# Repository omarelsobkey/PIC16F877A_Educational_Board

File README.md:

# Introduction
we can call it "PIC copy of Arduino". it was designed for educational purposes as I study microcontrollers this semester and the main microcontroller in this course is PIC16F877A.
this board supplies me with the most needed connections for me so allow me to mention them to you

# Features
1. 5x10 cm^2
2. ON/OFF Switch
3. Power input (7:20)v in 4 ways (terminal Block, USB, Power Adapter, Vin pin)
4. Outputs 5v, 3.3v
5. Header for all PIC GPIO pins
6. Programming pins header
7. UART communication using CH340 with jumpers to allow either connecting or disconnecting computer communication

# Versions
this is the 4th version of this board as I always seek additional improvements that will help me make the work easier
- 1st Version was only the main connection of the reset circuit and crystal
- 2nd version supported input power (7:20)v through terminal block
- 3rd version supported the dc jack and added some protection to the power circuit
- 4th and last version includes the features mentioned above

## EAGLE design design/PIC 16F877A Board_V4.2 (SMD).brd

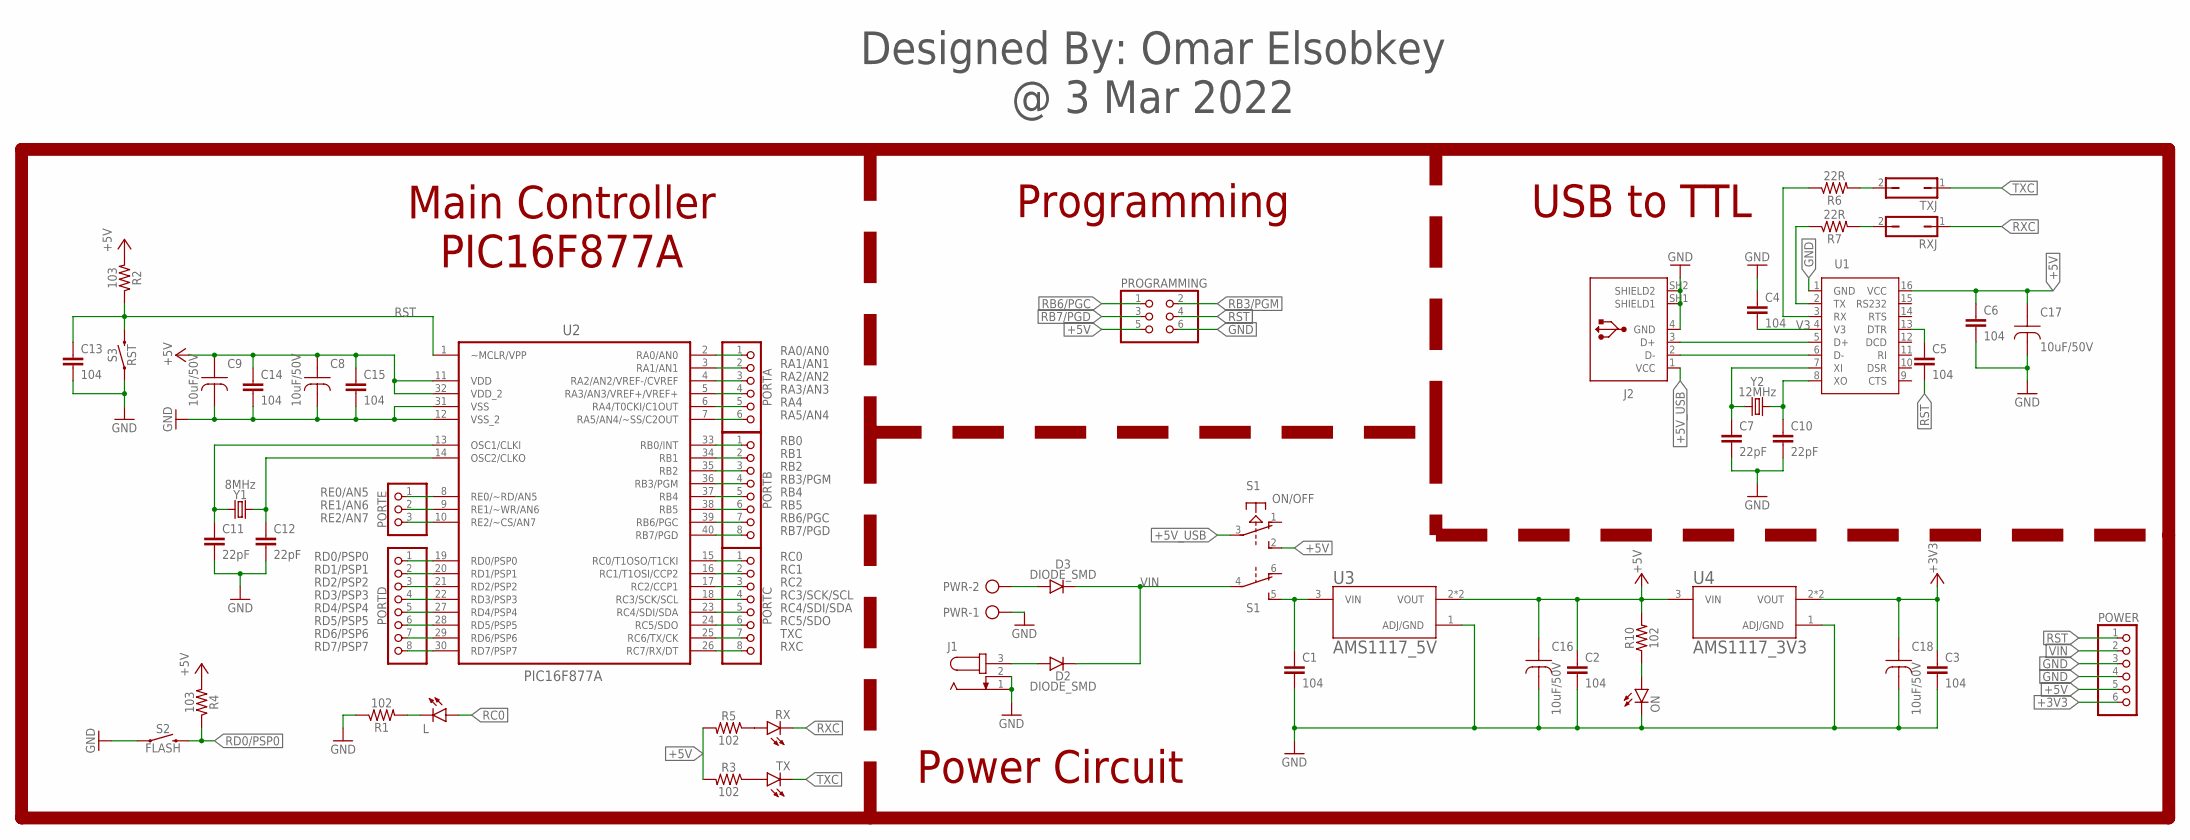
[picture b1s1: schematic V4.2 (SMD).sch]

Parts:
C1, C2, C3, C4, C5, C6, C13, C14, C15: 104; C0805K
C7, C10, C11, C12: 22pF; C0805K
C8, C9, C16, C17, C18: 10uF/50V; D5
D2, D3: DIODE_SMD; SMA/DO-214AC
J1: JACK-PLUG0; SPC4077
J2: 61729-1011; 61729-1011BLF
L: LEDCHIPLED_1206; CHIPLED_1206
ON: LEDCHIPLED_1206; CHIPLED_1206
PORTA: PINHD-1X6; 1X06
PORTB: PINHD-1X8; 1X08
PORTC: PINHD-1X8; 1X08
PORTD: PINHD-1X8; 1X08
PORTE: PINHD-1X3; 1X03
POWER: PINHD-1X6; 1X06
PROGRAMMING: PINHD-2X3; 2X03
PWR: 2P
R1, R3, R5, R10: 102; 1206
R2, R4: 103; 1206
R6, R7: 22R; 1206
RX: LEDCHIPLED_1206; CHIPLED_1206
RXJ: JP1Q; JP1
S1: ON/OFF; PVA2R
S2: FLASH; TACTILE_SWITCH_SMD_6.0X3.5MM
S3: RST; TACTILE_SWITCH_SMD_6.0X3.5MM
TX: LEDCHIPLED_1206; CHIPLED_1206
TXJ: JP1Q; JP1
U1: CH340G; SOP-16
U2: PIC16F877A; PDIP-40
U3: AMS1117_5V; SOT223
U4: AMS1117_3V3; SOT223
Y1: 8MHz; HC49U
Y2: 12MHz; HC49U

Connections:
+3V3: C3.1, C18.A, POWER.6, U4.2 (VOUT), U4.4 (VOUT)
+5V: C2.1, C6.1, C8.A, C9.A, C14.1, C15.1, C16.A, C17.A, POWER.5, PROGRAMMING.5, R2.2, R3.2, R4.2, R5.2, R10.2, S1.2 (S), U1.16 (VCC), U2.11 (VDD), U2.32 (VDD_2), U3.2 (VOUT), U3.4 (VOUT), U4.3 (VIN)
+5V_USB: J2.1 (VCC), S1.3
D+: J2.3 (D+), U1.5 (D+)
D-: J2.2 (D-), U1.6 (D-)
DTR: C5.1, U1.13 (DTR)
GND: C1.2, C2.2, C3.2, C4.1, C6.2, C7.2, C8.K, C9.K, C10.2, C11.2, C12.2, C13.2, C14.2, C15.2, C16.K, C17.K, C18.K, J1.1, J1.2, J2.4 (GND), J2.SH1 (SHIELD1), J2.SH2 (SHIELD2), ON.C, POWER.3, POWER.4, PROGRAMMING.6, PWR.1, R1.1, S2.1, S3.1, U1.1 (GND), U2.12 (VSS_2), U2.31 (VSS), U3.1 (ADJ/GND), U4.1 (ADJ/GND)
unnamed: R6.2, TXJ.2
unnamed: R3.1, TX.A
unnamed: R5.1, RX.A
unnamed: L.C, R1.2
unnamed: D2.2 (A), J1.3
unnamed: R7.2, RXJ.2
unnamed: D3.2 (A), PWR.2
unnamed: C1.1, S1.5 (S), U3.3 (VIN)
unnamed: ON.A, R10.1
OSC1: C11.1, U2.13 (OSC1/CLKI), Y1.2
OSC2: C12.1, U2.14 (OSC2/CLKO), Y1.1
RA0/AN0: PORTA.1, U2.2 (RA0/AN0)
RA1/AN1: PORTA.2, U2.3 (RA1/AN1)
RA2/AN2: PORTA.3, U2.4 (RA2/AN2/VREF-/CVREF)
RA3/AN3: PORTA.4, U2.5 (RA3/AN3/VREF+/VREF+)
RA4: PORTA.5, U2.6 (RA4/T0CKI/C1OUT)
RA5/AN4: PORTA.6, U2.7 (RA5/AN4/~SS/C2OUT)
RB0: PORTB.1, U2.33 (RB0/INT)
RB1: PORTB.2, U2.34 (RB1)
RB2: PORTB.3, U2.35 (RB2)
RB3/PGM: PORTB.4, PROGRAMMING.2, U2.36 (RB3/PGM)
RB4: PORTB.5, U2.37 (RB4)
RB5: PORTB.6, U2.38 (RB5)
RB6/PGC: PORTB.7, PROGRAMMING.1, U2.39 (RB6/PGC)
RB7/PGD: PORTB.8, PROGRAMMING.3, U2.40 (RB7/PGD)
RC0: L.A, PORTC.1, U2.15 (RC0/T1OSO/T1CKI)
RC1: PORTC.2, U2.16 (RC1/T1OSI/CCP2)
RC2: PORTC.3, U2.17 (RC2/CCP1)
RC3/SCK/SCL: PORTC.4, U2.18 (RC3/SCK/SCL)
RC4/SDI/SDA: PORTC.5, U2.23 (RC4/SDI/SDA)
RC5/SDO: PORTC.6, U2.24 (RC5/SDO)
RD0/PSP0: PORTD.1, R4.1, S2.2, U2.19 (RD0/PSP0)
RD1/PSP1: PORTD.2, U2.20 (RD1/PSP1)
RD2/PSP2: PORTD.3, U2.21 (RD2/PSP2)
RD3/PSP3: PORTD.4, U2.22 (RD3/PSP3)
RD4/PSP4: PORTD.5, U2.27 (RD4/PSP4)
RD5/PSP5: PORTD.6, U2.28 (RD5/PSP5)
RD6/PSP6: PORTD.7, U2.29 (RD6/PSP6)
RD7/PSP7: PORTD.8, U2.30 (RD7/PSP7)
RE0/AN5: PORTE.1, U2.8 (RE0/~RD/AN5)
RE1/AN6: PORTE.2, U2.9 (RE1/~WR/AN6)
RE2/AN7: PORTE.3, U2.10 (RE2/~CS/AN7)
RST: C5.2, C13.1, POWER.1, PROGRAMMING.4, R2.1, S3.2, U2.1 (~MCLR/VPP)
RX: R6.1, U1.3 (RX)
RXC: PORTC.8, RX.C, RXJ.1, U2.26 (RC7/RX/DT)
TX: R7.1, U1.2 (TX)
TXC: PORTC.7, TX.C, TXJ.1, U2.25 (RC6/TX/CK)
V3: C4.2, U1.4 (V3)
VIN: D2.1 (C), D3.1 (C), POWER.2, S1.4
XI: C7.1, U1.7 (XI), Y2.2
XO: C10.1, U1.8 (XO), Y2.1

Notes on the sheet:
Main Controller PIC16F877A
Power Circuit
Programming
Designed By: Omar Elsobkey @ 3 Mar 2022
USB to TTL

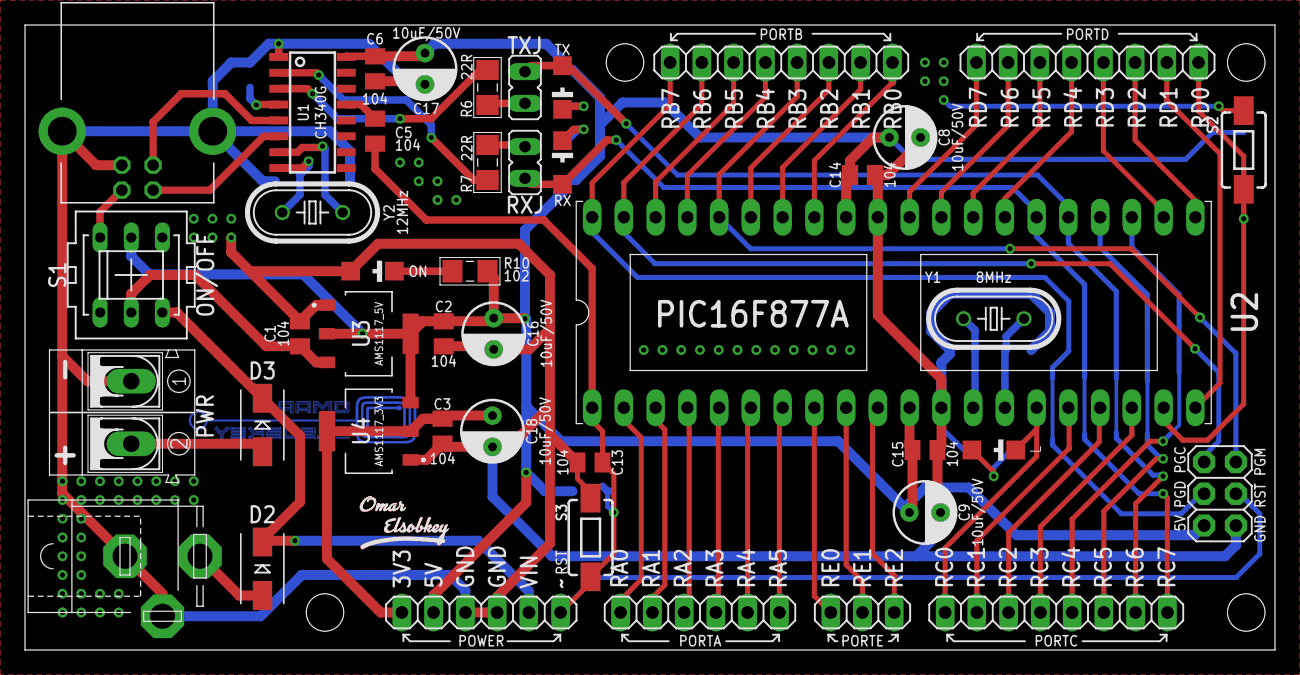
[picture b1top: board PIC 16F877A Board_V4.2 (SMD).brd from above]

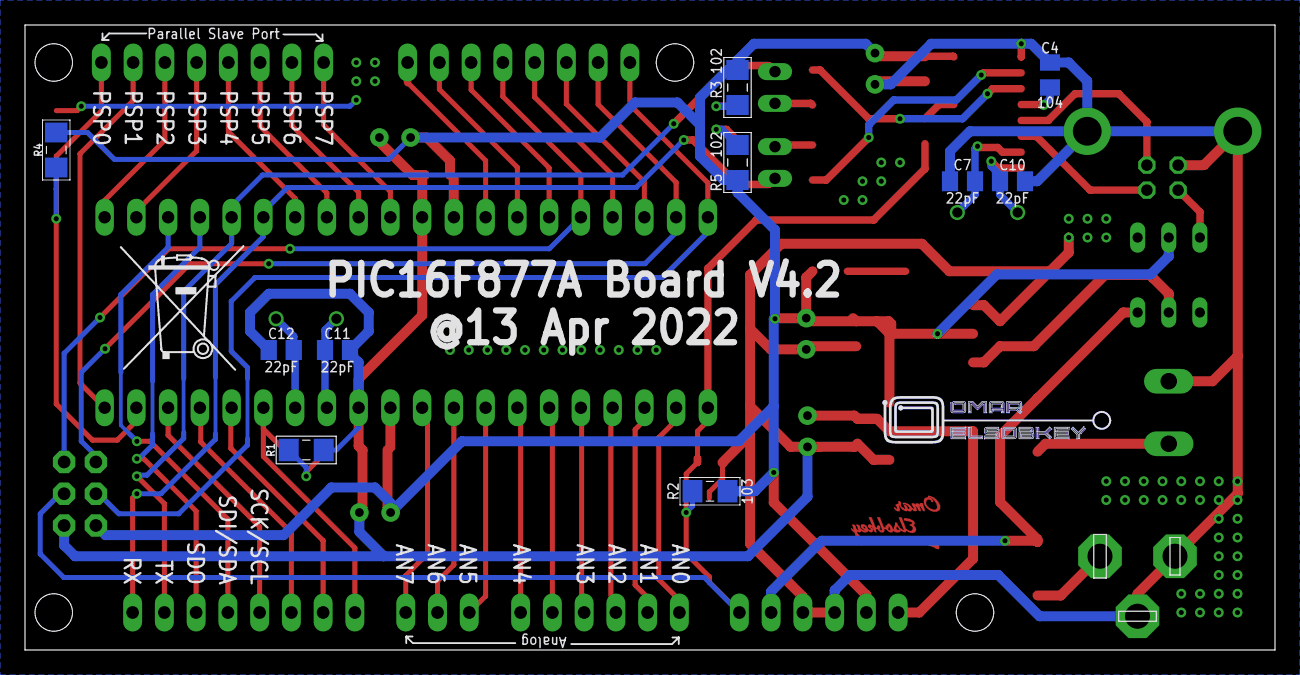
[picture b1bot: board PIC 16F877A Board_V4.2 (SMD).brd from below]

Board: 2 copper layers, 100.0 x 50.0 mm, 58 parts (13 on the bottom side), 58 nets.

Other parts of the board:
U$1: OMAR_ELSOBKEY_2_X1_T
U$2: OMAR_ELSOBKEY_2_X1_TP
U$3: OMAR_ELSOBKEY_1_X0.5_TN
U$4: MUELLTONNE_10.00
U$5: OMAR_ELSOBKEY_1_X0.5_T

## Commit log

2023-01-08 Rename PIC 16F877A Board_V4.2 (SMD).sch to design/PIC 16F877A Board_V4.2 (SMD).sch
2023-01-08 Oragnize the repo
2023-01-08 Rename Files

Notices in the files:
parts and their libraries:
SparkFun-Resistors: Licensing: Creative Commons ShareAlike 4.0 International - https://creativecommons.org/licenses/by-sa/4.0
